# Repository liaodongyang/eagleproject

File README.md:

# eagleproject
Eagle PCB project

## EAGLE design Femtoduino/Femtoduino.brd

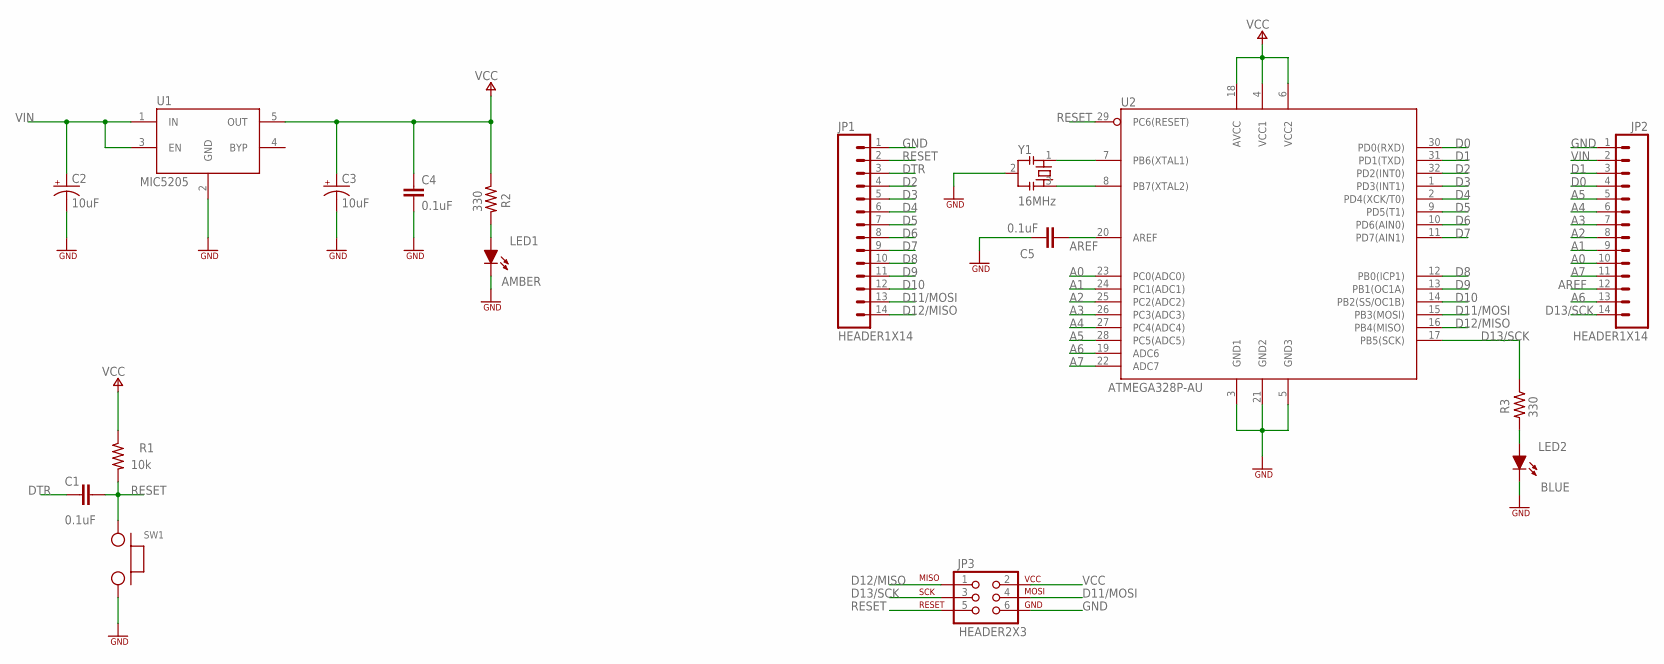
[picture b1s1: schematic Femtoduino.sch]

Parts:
C1, C4, C5: 0.1uF; SMD0603
C2, C3: 10uF; EIA3216
JP1, JP2: HEADER1X14; 1X14
JP3: HEADER2X3; 2X3
LED1: AMBER; LED_0603
LED2: BLUE; LED_0805
R1: 10k; SMD0603
R2, R3: 330; SMD0603
SW1: SWITCH; SWITCH-SPST
U1: MIC5205; SOT23-5
U2: ATMEGA328P-AU; TQFP32
Y1: 16MHz; CSTCE

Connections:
A0: JP2.10, U2.23 (PC0(ADC0))
A1: JP2.9, U2.24 (PC1(ADC1))
A2: JP2.8, U2.25 (PC2(ADC2))
A3: JP2.7, U2.26 (PC3(ADC3))
A4: JP2.6, U2.27 (PC4(ADC4))
A5: JP2.5, U2.28 (PC5(ADC5))
A6: JP2.13, U2.19 (ADC6)
A7: JP2.11, U2.22 (ADC7)
AREF: C5.1, JP2.12, U2.20 (AREF)
D0: JP2.4, U2.30 (PD0(RXD))
D1: JP2.3, U2.31 (PD1(TXD))
D2: JP1.4, U2.32 (PD2(INT0))
D3: JP1.5, U2.1 (PD3(INT1))
D4: JP1.6, U2.2 (PD4(XCK/T0))
D5: JP1.7, U2.9 (PD5(T1))
D6: JP1.8, U2.10 (PD6(AIN0))
D7: JP1.9, U2.11 (PD7(AIN1))
D8: JP1.10, U2.12 (PB0(ICP1))
D9: JP1.11, U2.13 (PB1(OC1A))
D10: JP1.12, U2.14 (PB2(SS/OC1B))
D11/MOSI: JP1.13, JP3.4, U2.15 (PB3(MOSI))
D12/MISO: JP1.14, JP3.1, U2.16 (PB4(MISO))
D13/SCK: JP2.14, JP3.3, R3.1, U2.17 (PB5(SCK))
DTR: C1.1, JP1.3
GND: C2.C (-), C3.C (-), C4.2, C5.2, JP1.1, JP2.1, JP3.6, LED1.C, LED2.C, SW1.2, U1.2 (GND), U2.3 (GND1), U2.5 (GND3), U2.21 (GND2), Y1.2
unnamed: LED1.A, R2.2
unnamed: U2.7 (PB6(XTAL1)), Y1.1
unnamed: U2.8 (PB7(XTAL2)), Y1.3
unnamed: LED2.A, R3.2
RESET: C1.2, JP1.2, JP3.5, R1.2, SW1.1, U2.29 (PC6(RESET))
VCC: C3.A (+), C4.1, JP3.2, R1.1, R2.1, U1.5 (OUT), U2.4 (VCC1), U2.6 (VCC2), U2.18 (AVCC)
VIN: C2.A (+), JP2.2, U1.1 (IN), U1.3 (EN)

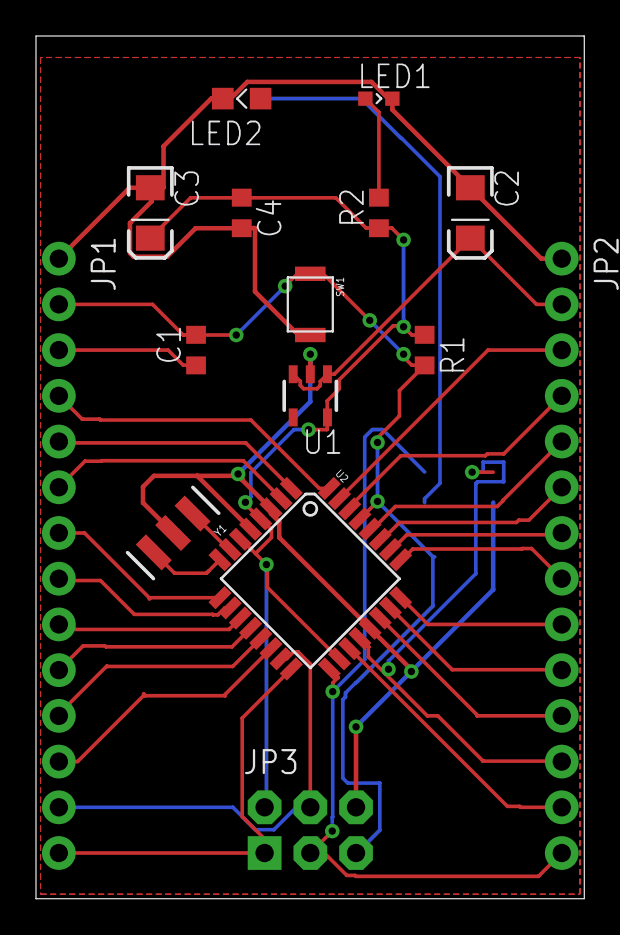
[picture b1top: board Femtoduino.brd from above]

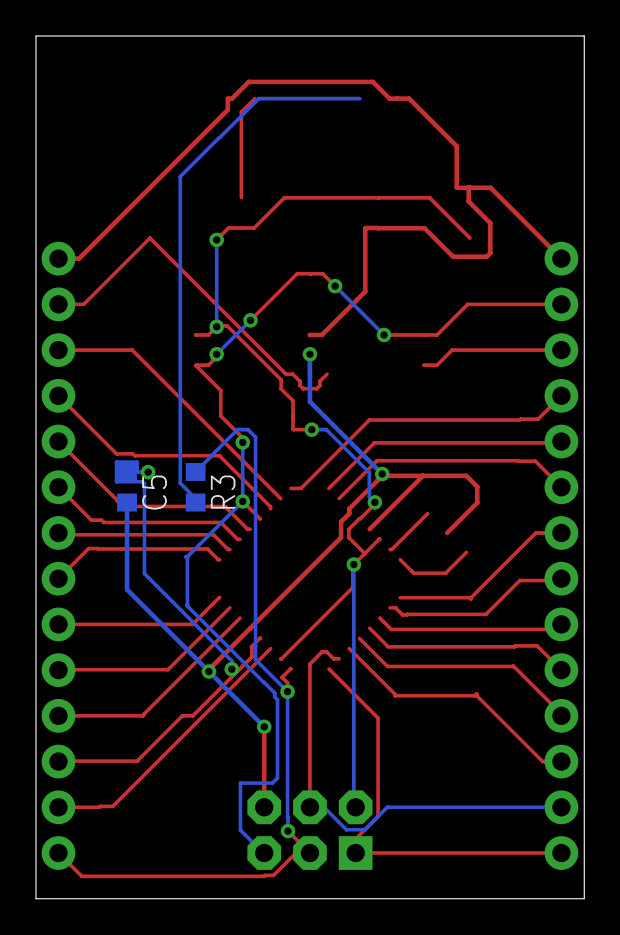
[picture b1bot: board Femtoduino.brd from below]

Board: 2 copper layers, 30.5 x 47.9 mm, 17 parts (2 on the bottom side), 32 nets.

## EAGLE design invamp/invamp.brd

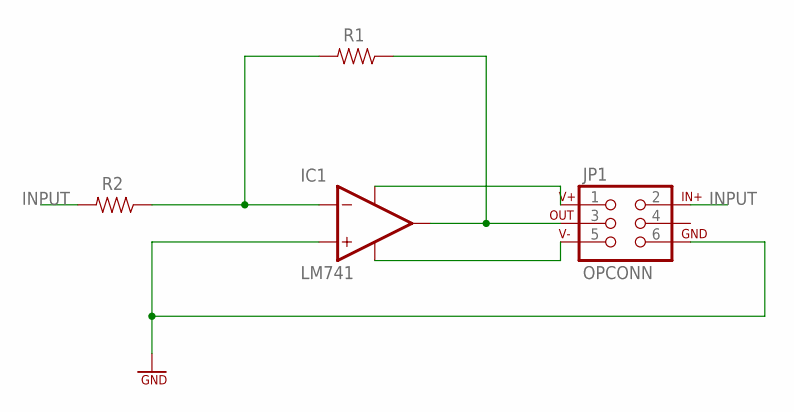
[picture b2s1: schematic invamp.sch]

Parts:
IC1: LM741; SO08
JP1: OPCONN; 2X3
R1, R2: RES_0603; SMD0603

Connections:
GND: IC1.3 (IN+), JP1.6
INPUT: JP1.2, R2.2
unnamed: IC1.6 (OUT), JP1.3, R1.1
unnamed: IC1.2 (IN-), R1.2, R2.1
unnamed: IC1.7 (V+), JP1.1
unnamed: IC1.4 (V-), JP1.5

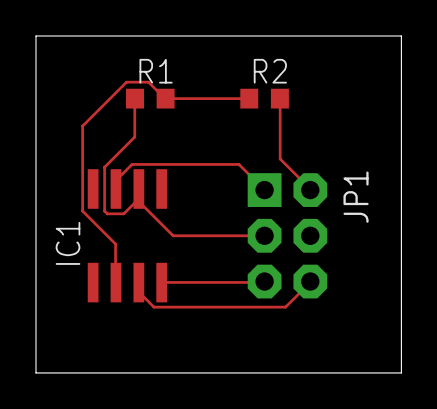
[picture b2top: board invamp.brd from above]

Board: 2 copper layers, 20.3 x 18.7 mm, 4 parts (0 on the bottom side), 6 nets.

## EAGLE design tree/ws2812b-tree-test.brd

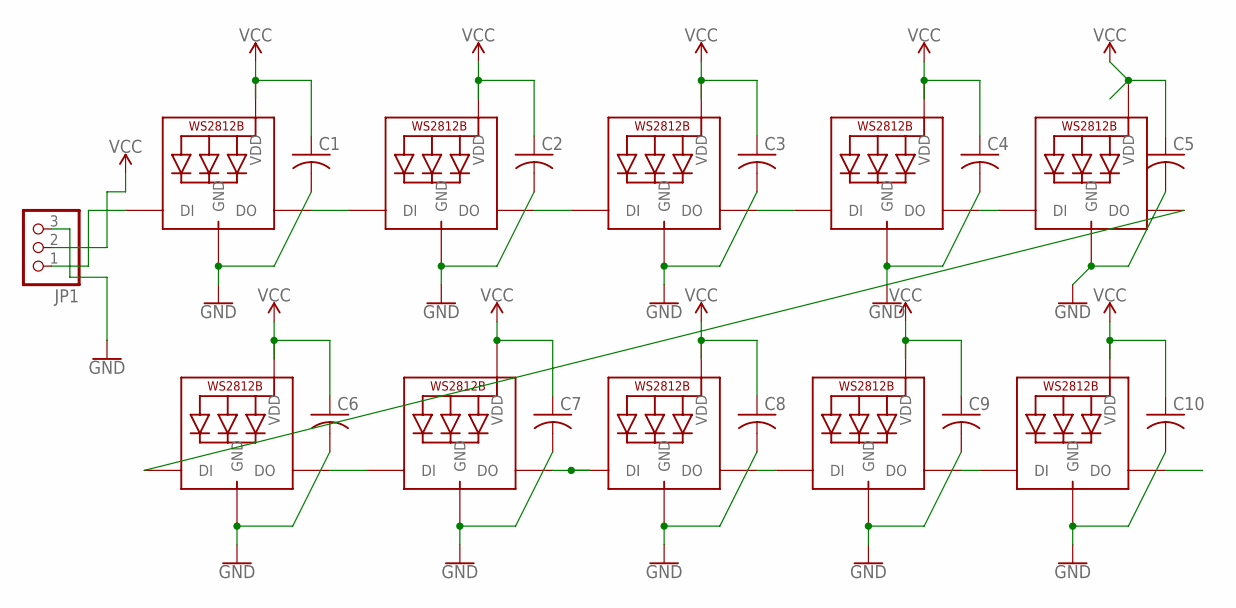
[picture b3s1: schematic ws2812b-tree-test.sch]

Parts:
C1, C2, C3, C4, C5, C6, C7, C8, C9, C10: C-USC3216; C3216
JP1: PINHD-1X3; 1X03
LED1, LED2, LED3, LED4, LED5, LED6, LED7, LED8, LED9, LED10: WS2812B5050; WS2812B

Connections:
GND: C1.2, C2.2, C3.2, C4.2, C5.2, C6.2, C7.2, C8.2, C9.2, C10.2, JP1.3, LED1.3-GND (GND), LED2.3-GND (GND), LED3.3-GND (GND), LED4.3-GND (GND), LED5.3-GND (GND), LED6.3-GND (GND), LED7.3-GND (GND), LED8.3-GND (GND), LED9.3-GND (GND), LED10.3-GND (GND)
unnamed: LED2.2-DOUT (DO), LED3.4-DIN (DI)
unnamed: LED1.2-DOUT (DO), LED2.4-DIN (DI)
unnamed: LED3.2-DOUT (DO), LED4.4-DIN (DI)
unnamed: LED4.2-DOUT (DO), LED5.4-DIN (DI)
unnamed: LED6.2-DOUT (DO), LED7.4-DIN (DI)
unnamed: LED5.2-DOUT (DO), LED6.4-DIN (DI)
unnamed: LED7.2-DOUT (DO), LED8.4-DIN (DI)
unnamed: LED8.2-DOUT (DO), LED9.4-DIN (DI)
unnamed: LED9.2-DOUT (DO), LED10.4-DIN (DI)
unnamed: JP1.1, LED1.4-DIN (DI)
VCC: C1.1, C2.1, C3.1, C4.1, C5.1, C6.1, C7.1, C8.1, C9.1, C10.1, JP1.2, LED1.1-VDD (VDD), LED2.1-VDD (VDD), LED3.1-VDD (VDD), LED4.1-VDD (VDD), LED5.1-VDD (VDD), LED6.1-VDD (VDD), LED7.1-VDD (VDD), LED8.1-VDD (VDD), LED9.1-VDD (VDD), LED10.1-VDD (VDD)

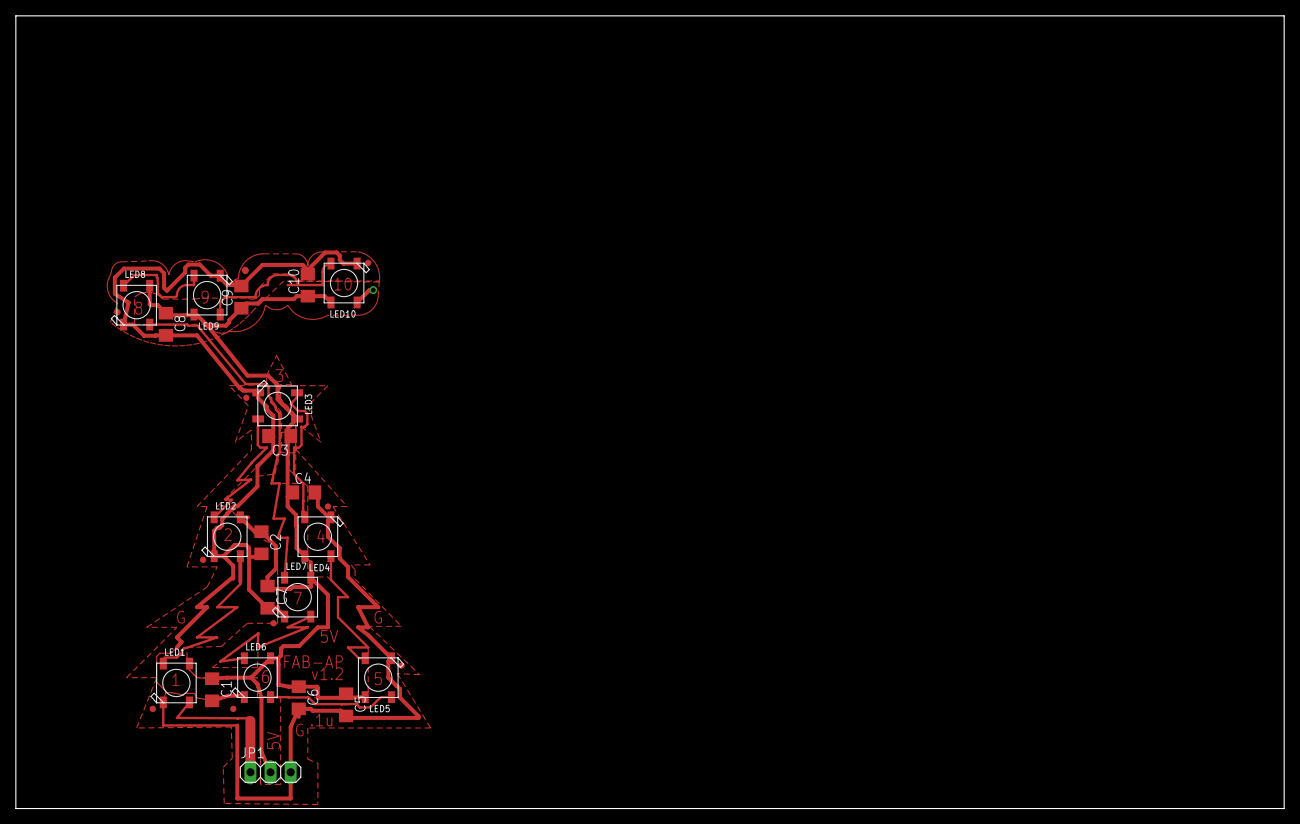
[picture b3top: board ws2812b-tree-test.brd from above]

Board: 2 copper layers, 160.0 x 100.0 mm, 21 parts (0 on the bottom side), 12 nets.

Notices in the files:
parts and their libraries:
SparkFun-PowerSymbols: Licensing: Creative Commons ShareAlike 4.0 International - https://creativecommons.org/licenses/by-sa/4.0
